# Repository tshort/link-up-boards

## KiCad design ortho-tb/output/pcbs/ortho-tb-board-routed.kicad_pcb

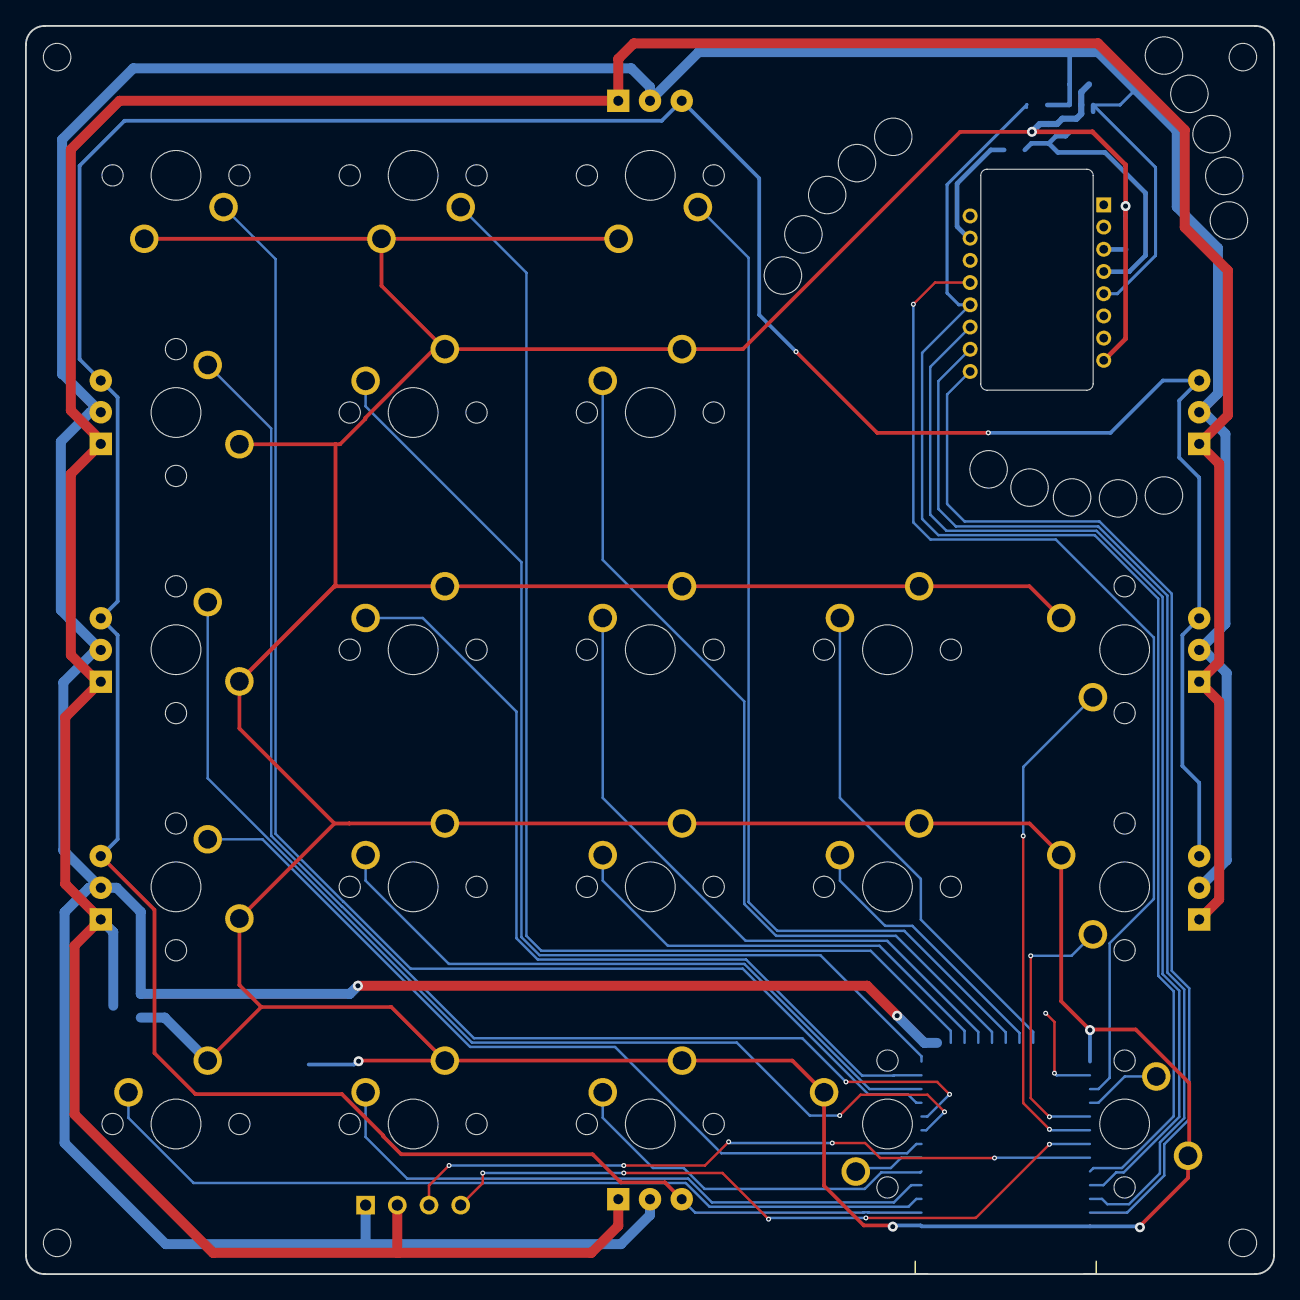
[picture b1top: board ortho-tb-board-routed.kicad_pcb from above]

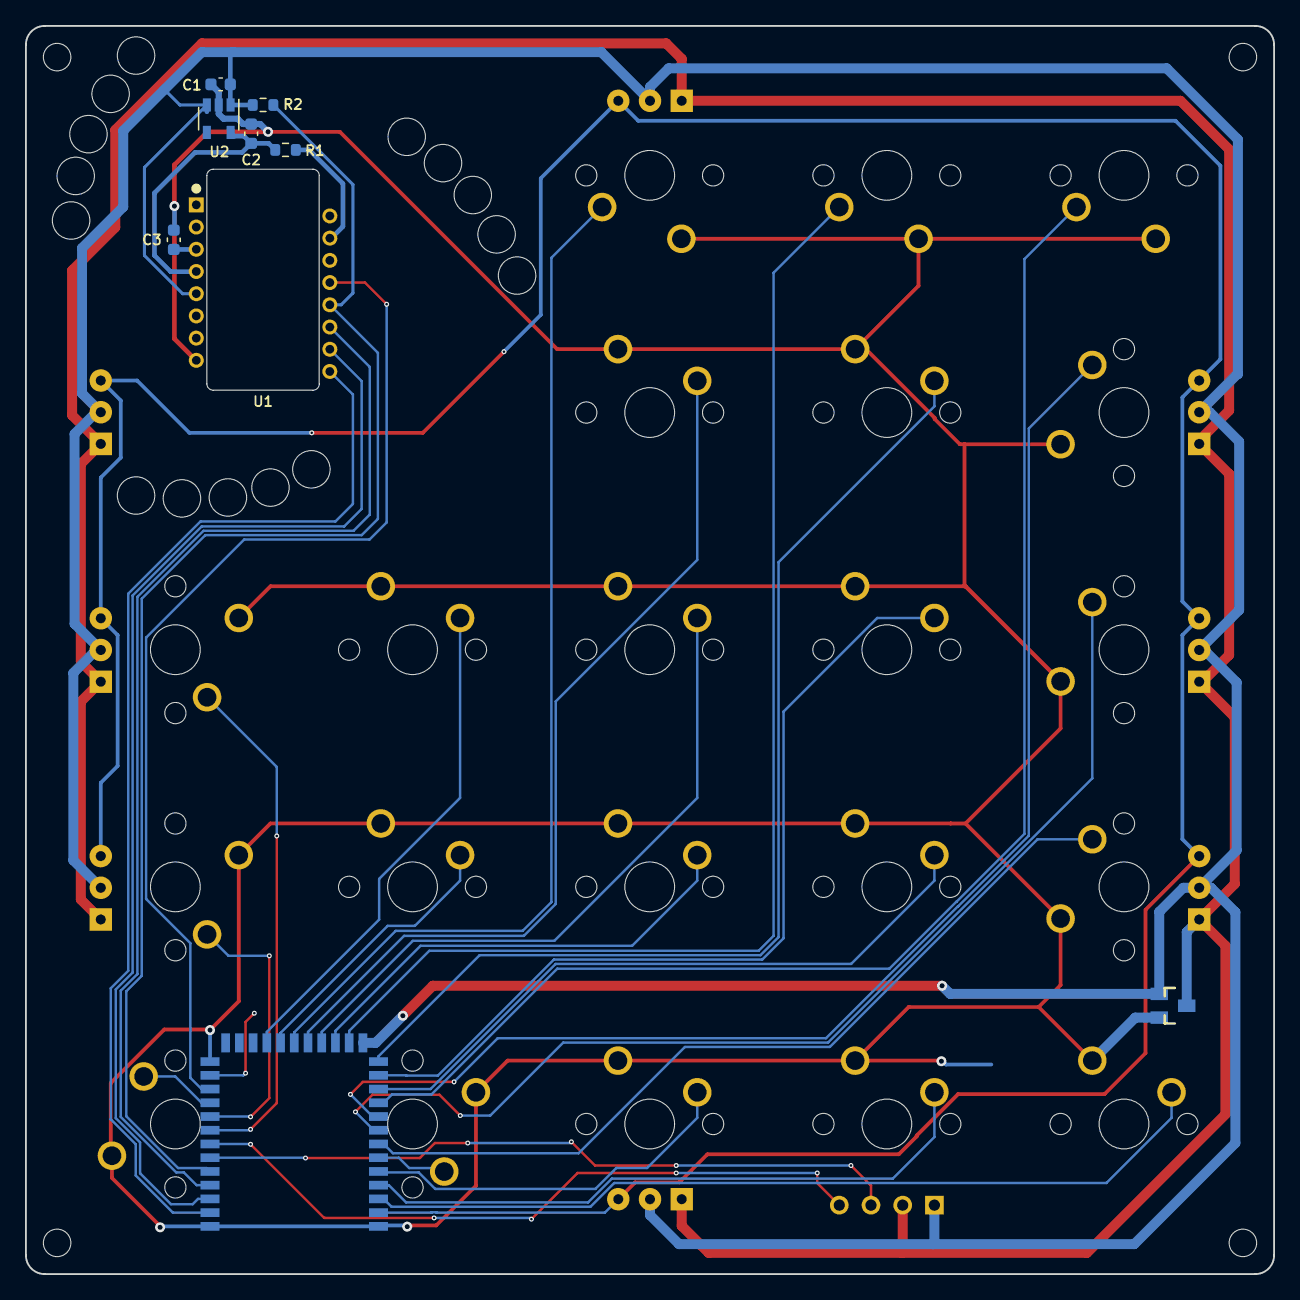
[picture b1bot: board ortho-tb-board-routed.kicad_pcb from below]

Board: 2 copper layers, 100.0 x 100.0 mm, 28 parts (7 on the bottom side), 3 nets.

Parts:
C1: 0.1u; C_0603_1608Metric
C2: 1u; C_0603_1608Metric
C3: 4.7u; C_0603_1608Metric
R1: 39; R_0603_1608Metric
R2: 10k; R_0603_1608Metric
S1, S2, S3, S4, S5, S6, S7, S8, S9, S10, S11, S12, S13, S14, S15, S16, S17, S18, S19, S20, S21: MX
U1: PMW3360
U2: TCR2EF19; SOT-23-5

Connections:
GND: C1.1, C2.2, C3.2, S1.1, S2.1, S3.1, S4.1, S5.1, S6.1, S7.1, S8.1, S9.1, S10.1, S11.1, S12.1, S13.1, S14.1, S15.1, S16.1, S17.1, S18.1, S19.1, S20.1, S21.1, U1.8, U2.2
MISO: R2.2, U1.12
VCC: C1.2, R2.1, U1.5, U2.1, U2.3

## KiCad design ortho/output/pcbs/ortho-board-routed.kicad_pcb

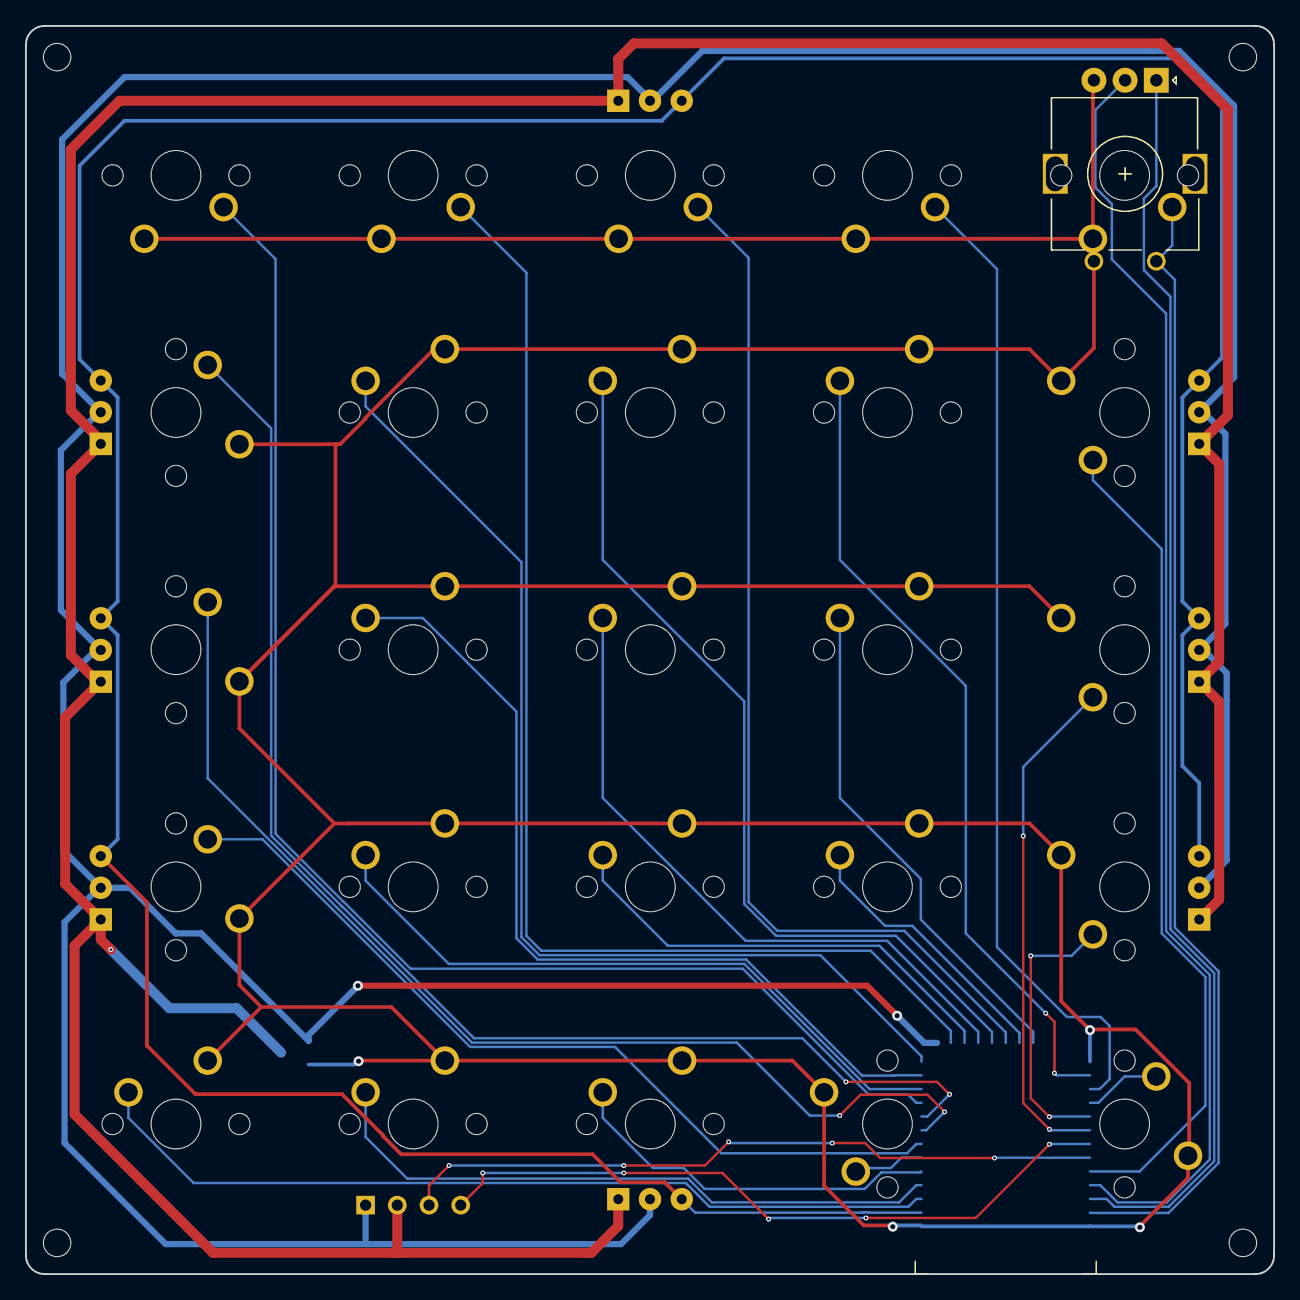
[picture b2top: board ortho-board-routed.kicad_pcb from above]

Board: 2 copper layers, 100.0 x 100.0 mm, 26 parts (0 on the bottom side), 2 nets.

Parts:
ROT1: rotary_encoder
S1, S2, S3, S4, S5, S6, S7, S8, S9, S10, S11, S12, S13, S14, S15, S16, S17, S18, S19, S20, S21, S22, S23, S24, S25: MX

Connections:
GND: ROT1.2, ROT1.B, S1.1, S2.1, S3.1, S4.1, S5.1, S6.1, S7.1, S8.1, S9.1, S10.1, S11.1, S12.1, S13.1, S14.1, S15.1, S16.1, S17.1, S18.1, S19.1, S20.1, S21.1, S22.1, S23.1, S24.1, S25.1
m_c5_r5: ROT1.1, S25.2
